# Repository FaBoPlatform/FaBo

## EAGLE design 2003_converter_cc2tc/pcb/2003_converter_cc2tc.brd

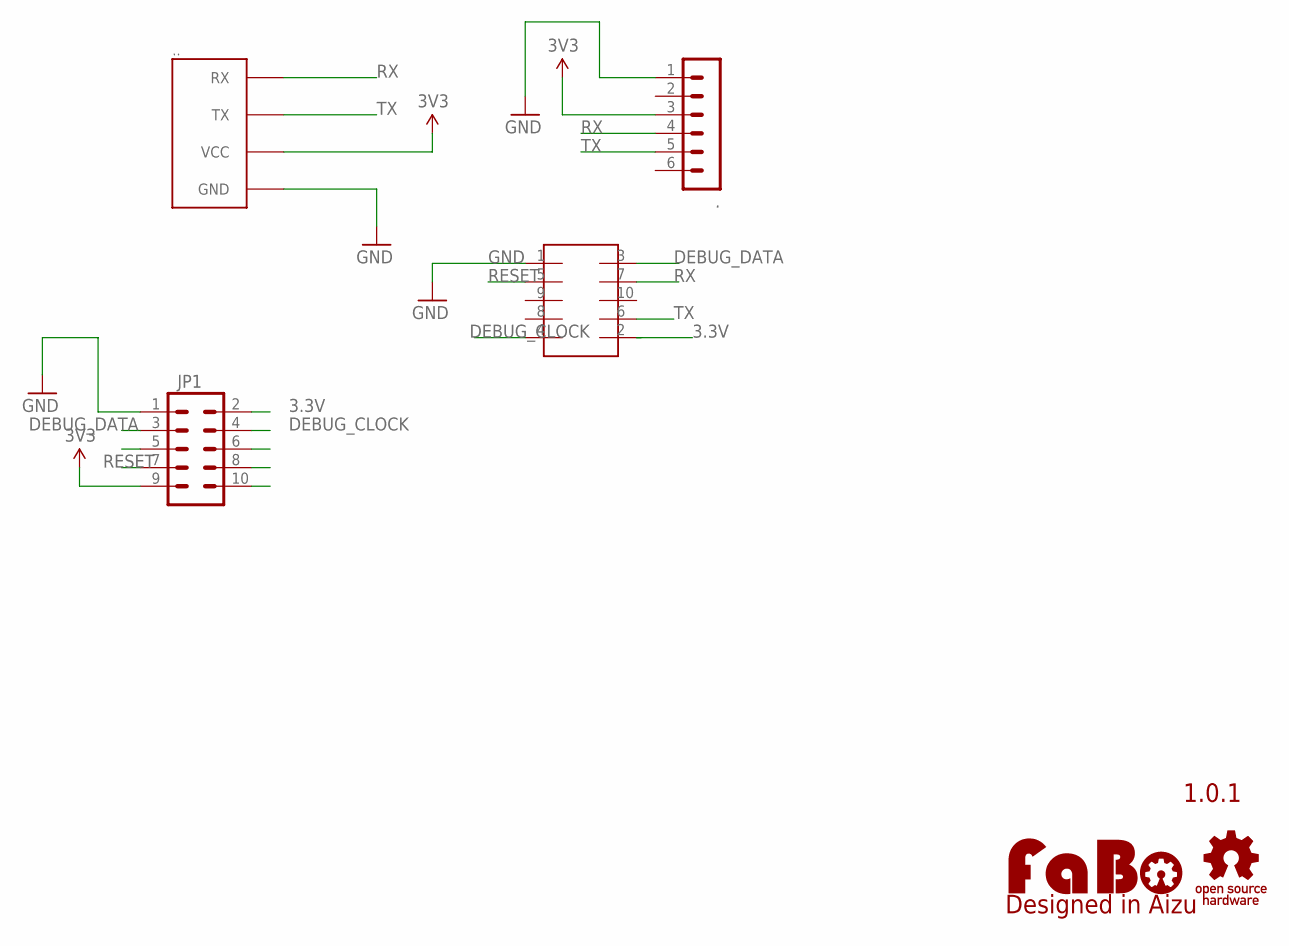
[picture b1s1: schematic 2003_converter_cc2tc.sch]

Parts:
.: MA06-1
..: FABO_BRICK_SERIAL-S04B-PASK-2; FABO_BRICK_SERIAL_S04B-PASK-2
JP1: M05X2SHD; 2X5-SHROUDED
U$1: LOGO_OSHW-M_BOTTOM; LOGO_OSHW_M_BOTTOM
U$2: LOGO_FABO-M; LOGO_FABO_MS
U$4: TC-2050-SOCKET

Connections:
3.3V: JP1.2, U$4.2
3V3: ..3, ...VCC, JP1.9
CSN: JP1.5
DEBUG_CLOCK: JP1.4, U$4.4
DEBUG_DATA: JP1.3, U$4.3
GND: ..1, ...GND, JP1.1, U$4.1
MISO: JP1.10
MOSI: JP1.8
RESET: JP1.7, U$4.5
RX: ..4, ...RX, U$4.7
SCLK: JP1.6
TX: ..5, ...TX, U$4.6

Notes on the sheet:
1.0.1

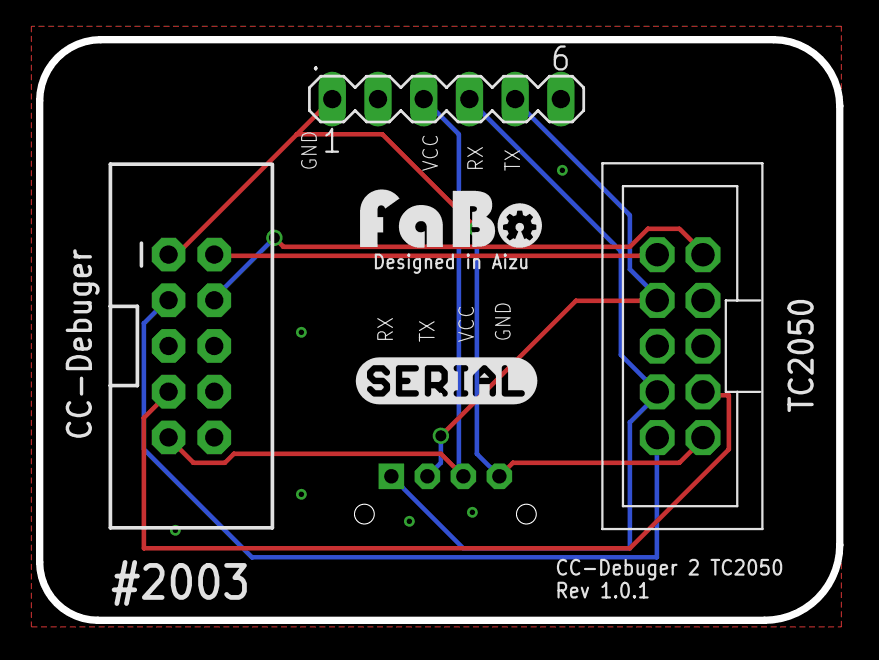
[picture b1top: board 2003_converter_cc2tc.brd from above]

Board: 2 copper layers, 44.4 x 32.3 mm, 7 parts (0 on the bottom side), 8 nets.

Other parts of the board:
U$5: LOGO_SILK_SERIAL2

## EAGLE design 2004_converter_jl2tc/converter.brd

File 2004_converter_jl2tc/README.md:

# #2004 Jlink 2 TagConnector

## Overview

JLinkからTagConnecterへの変換をおこないます。

## 回路図

## Github

https://github.com/FaBoPlatform/FaBo/tree/master/2004_converter_jl2tc

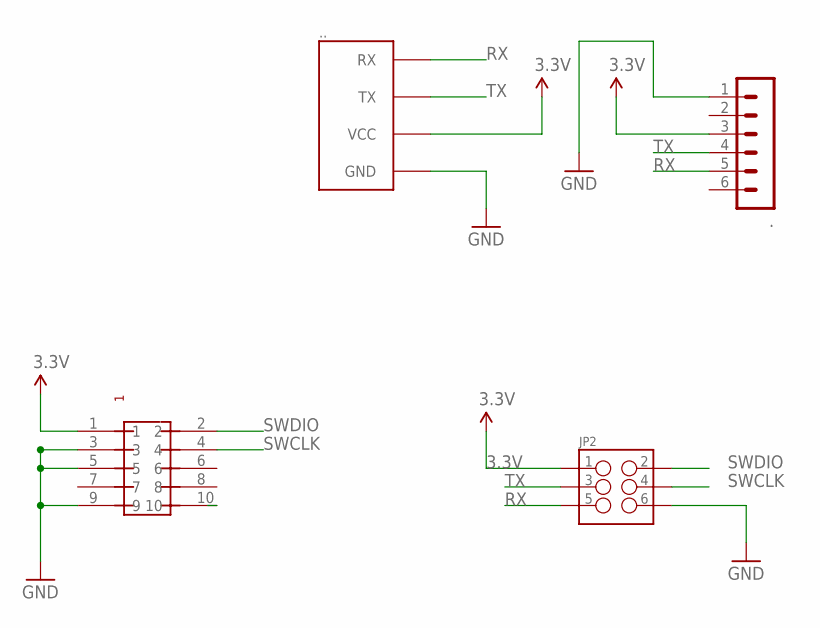
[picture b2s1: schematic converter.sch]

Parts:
.: MA06-1
..: FABO_BRICK_SERIAL-S04B-PASK-2; FABO_BRICK_SERIAL_S04B-PASK-2
JP2: M03X2; 2X3-SHROUDED
U$5: PIN-HEADER-SMT(1.27MM)2X5

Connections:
3.3V: ..3, ...VCC, JP2.1, U$5.1
GND: ..1, ...GND, JP2.6, U$5.3, U$5.5, U$5.9
RESET: U$5.10
RX: ..5, ...RX, JP2.5
SWCLK: JP2.4, U$5.4
SWDIO: JP2.2, U$5.2
TX: ..4, ...TX, JP2.3

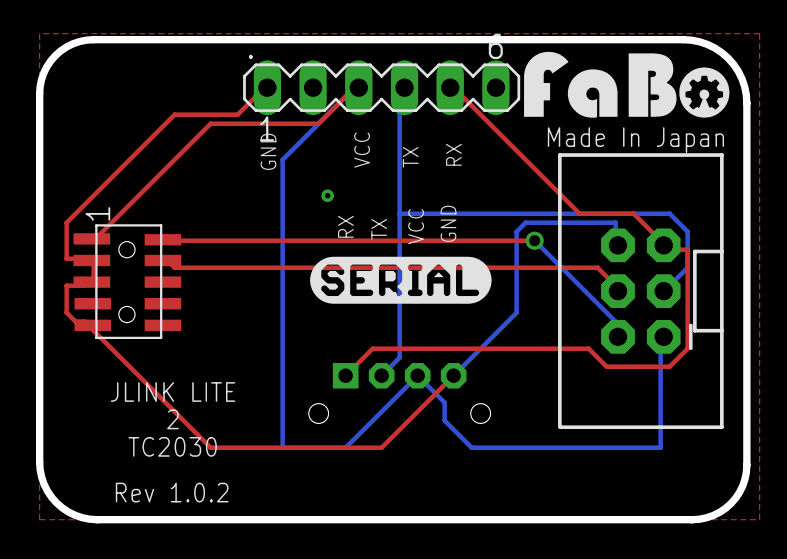
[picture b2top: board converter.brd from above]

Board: 2 copper layers, 39.3 x 26.7 mm, 6 parts (0 on the bottom side), 6 nets.

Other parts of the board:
U$1: LOGO_FABO_M
U$2: LOGO_SILK_SERIAL2

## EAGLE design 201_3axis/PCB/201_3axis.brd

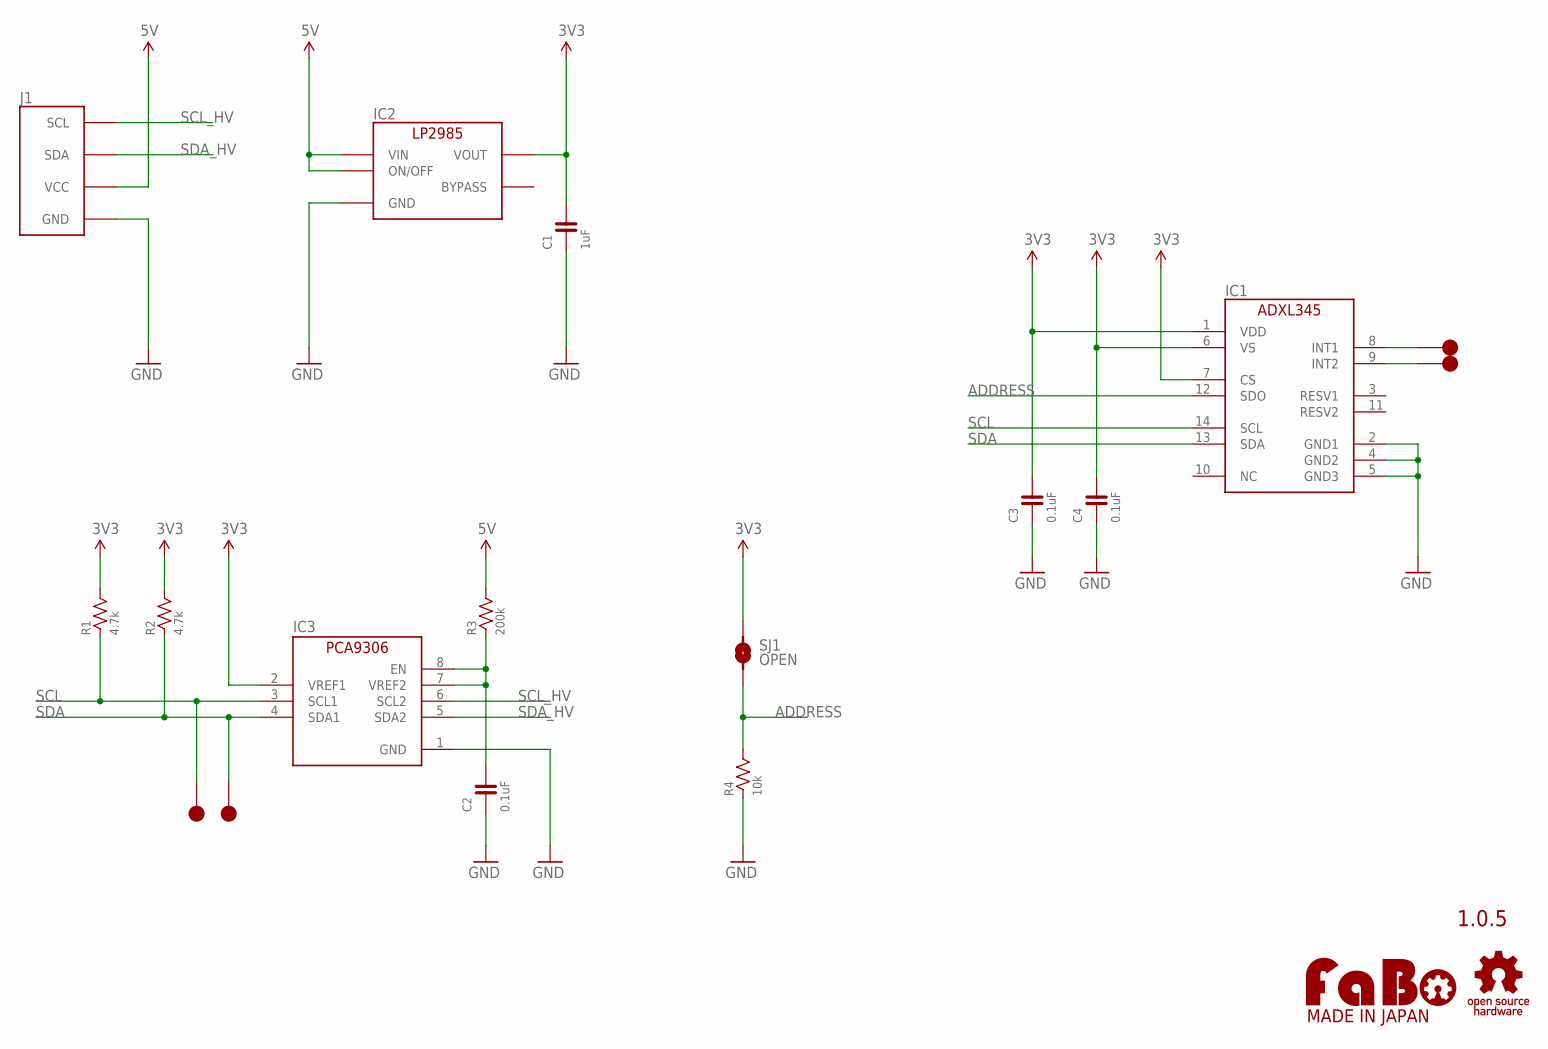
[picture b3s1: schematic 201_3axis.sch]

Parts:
C1: 1uF; 0603
C2, C3, C4: 0.1uF; 0603
IC1: AD-ADXL345; ANALOGDEVICES-ADXL345
IC2: LP2985-33DBV; SOT-23-5
IC3: PCA9306GM; XQFN8
J1: FABO_BRICK_I2C
R1, R2: 4.7k; 0603
R3: 200k; 0603
R4: 10k; 0603
SJ1: OPEN; SMD-JUMPER-2
TP1, TP2, TP3, TP4: TP-15
U$2: LOGO_OSHW-M_BOTTOM; LOGO_OSHW_M_BOTTOM
U$3: LOGO_FABO-M; LOGO_FABO_MS

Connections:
3V3: C1.2, C3.2, C4.2, IC1.1 (VDD), IC1.6 (VS), IC1.7 (CS), IC2.5 (VOUT), IC3.2 (VREF1), R1.2, R2.2, SJ1.1
5V: IC2.1 (VIN), IC2.3 (ON/OFF), J1.VCC, R3.2
ADDRESS: IC1.12 (SDO), R4.2, SJ1.2
GND: C1.1, C2.1, C3.1, C4.1, IC1.2 (GND1), IC1.4 (GND2), IC1.5 (GND3), IC2.2 (GND), IC3.1 (GND), J1.GND, R4.1
unnamed: C2.2, IC3.7 (VREF2), IC3.8 (EN), R3.1
unnamed: IC1.8 (INT1), TP3.1
unnamed: IC1.9 (INT2), TP4.1
SCL: IC1.14 (SCL), IC3.3 (SCL1), R1.1, TP2.1
SCL_HV: IC3.6 (SCL2), J1.SCL
SDA: IC1.13 (SDA), IC3.4 (SDA1), R2.1, TP1.1
SDA_HV: IC3.5 (SDA2), J1.SDA

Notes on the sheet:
1.0.5

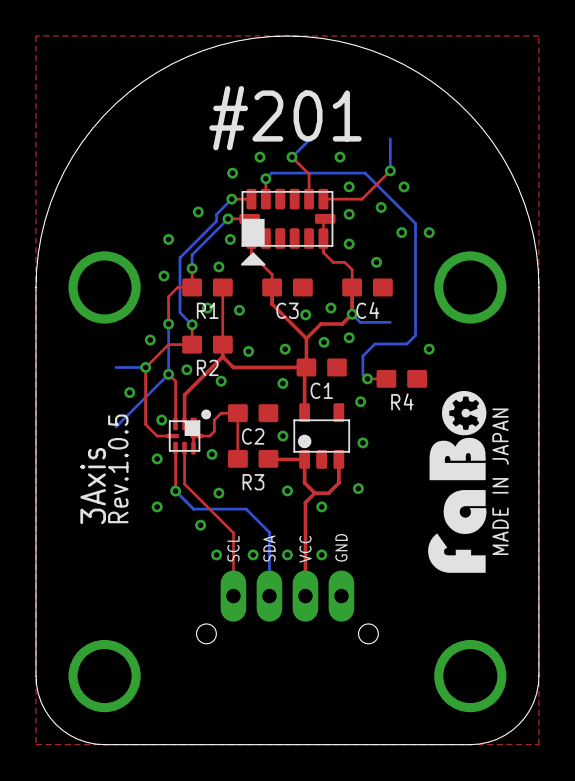
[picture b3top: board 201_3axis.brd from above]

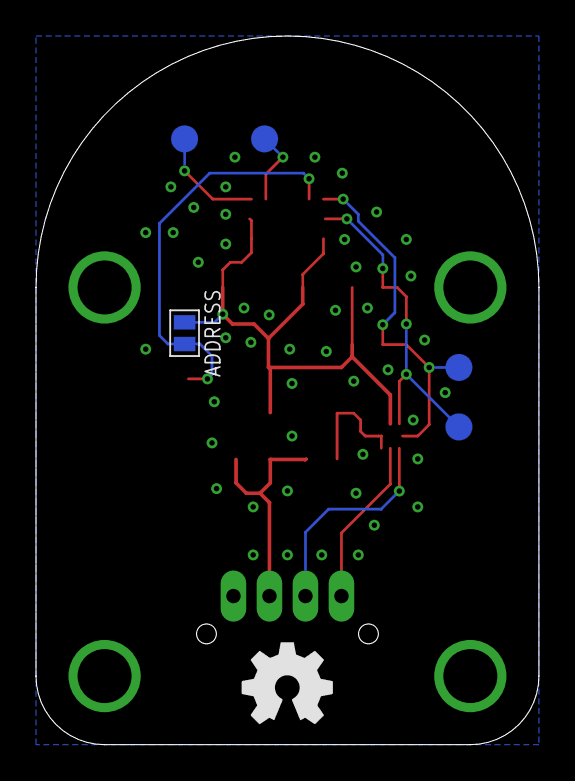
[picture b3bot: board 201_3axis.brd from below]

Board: 2 copper layers, 27.9 x 39.4 mm, 19 parts (5 on the bottom side), 11 nets.

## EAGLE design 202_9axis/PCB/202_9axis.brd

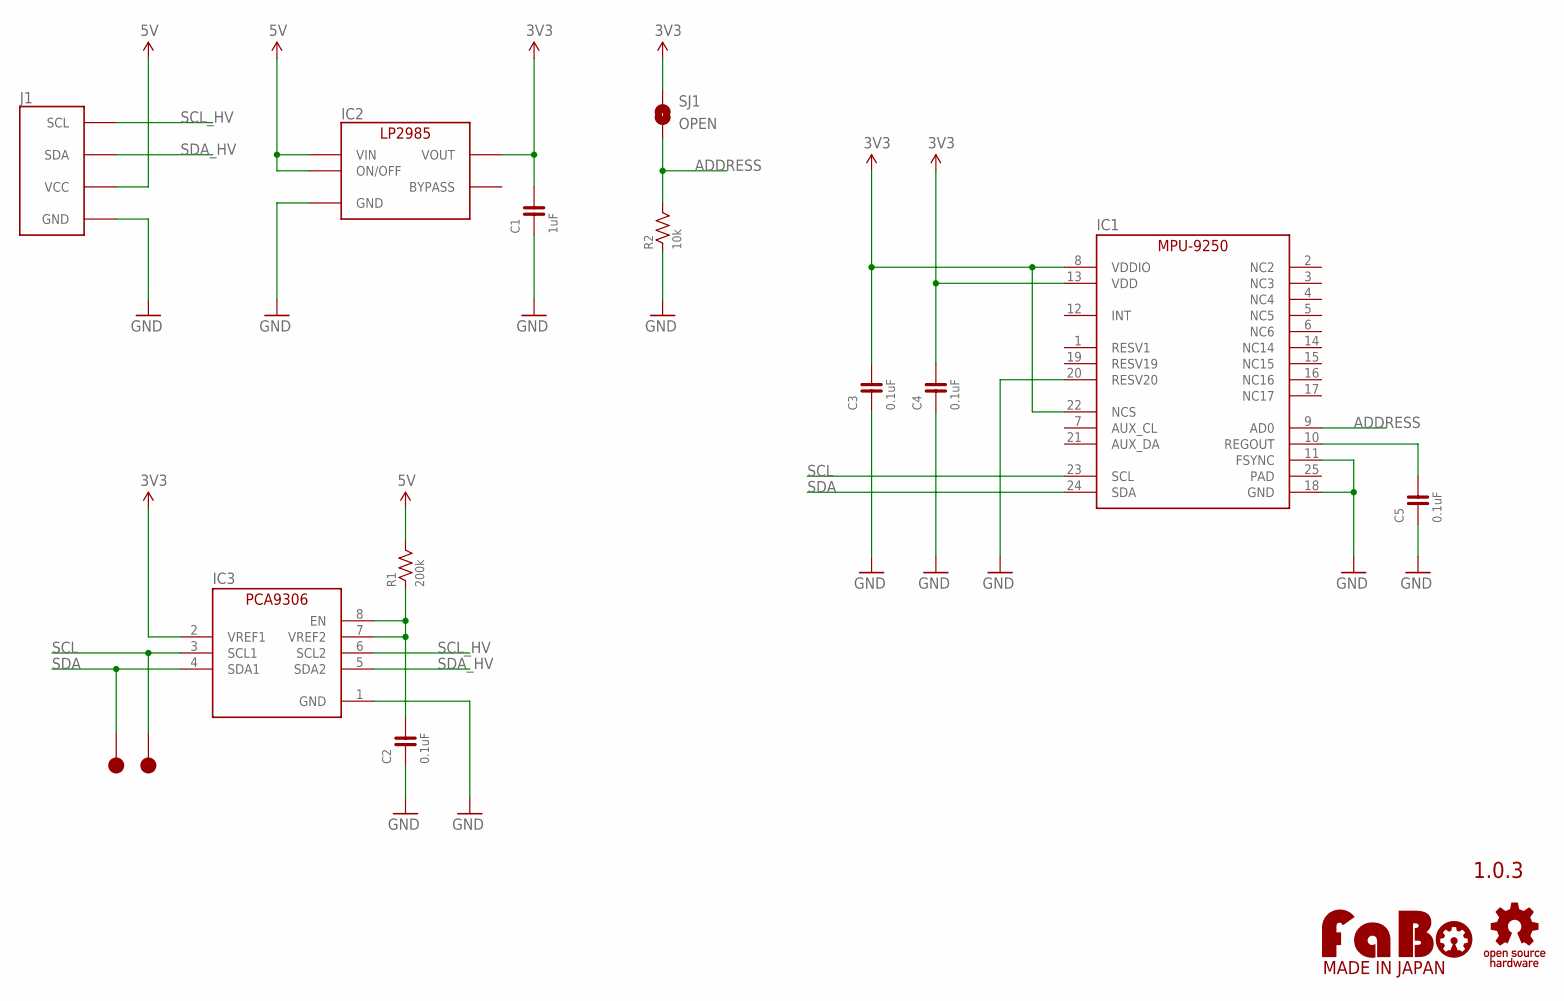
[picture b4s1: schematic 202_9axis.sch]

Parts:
C1: 1uF; 0603
C2, C3, C4, C5: 0.1uF; 0603
IC1: IS-MPU9250; INVENSENSE-MPU9250
IC2: TI-LP2985-33DBVR; TI-LP2985
IC3: PCA9306DQER; X2SON
J1: FABO_BRICK_I2C
R1: 200k; 0603
R2: 10k; 0603
SJ1: OPEN; SMD-JUMPER-2-OPEN
TP1, TP2: TP-10
U$2: LOGO_OSHW-M_BOTTOM; LOGO_OSHW_M_BOTTOM
U$3: LOGO_FABO-M; LOGO_FABO_MS

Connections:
3V3: C1.2, C3.2, C4.2, IC1.8 (VDDIO), IC1.13 (VDD), IC1.22 (NCS), IC2.5 (VOUT), IC3.2 (VREF1), SJ1.1
5V: IC2.1 (VIN), IC2.3 (ON/OFF), J1.VCC, R1.2
ADDRESS: IC1.9 (AD0), R2.2, SJ1.2
GND: C1.1, C2.1, C3.1, C4.1, C5.1, IC1.11 (FSYNC), IC1.18 (GND), IC1.20 (RESV20), IC2.2 (GND), IC3.1 (GND), J1.GND, R2.1
unnamed: C2.2, IC3.7 (VREF2), IC3.8 (EN), R1.1
REGOUT: C5.2, IC1.10 (REGOUT)
SCL: IC1.23 (SCL), IC3.3 (SCL1), TP2.1
SCL_HV: IC3.6 (SCL2), J1.SCL
SDA: IC1.24 (SDA), IC3.4 (SDA1), TP1.1
SDA_HV: IC3.5 (SDA2), J1.SDA

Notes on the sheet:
1.0.3

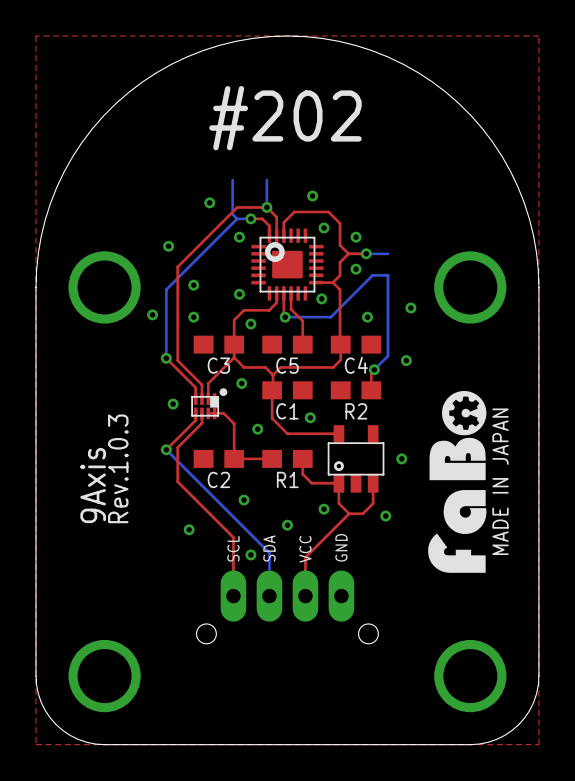
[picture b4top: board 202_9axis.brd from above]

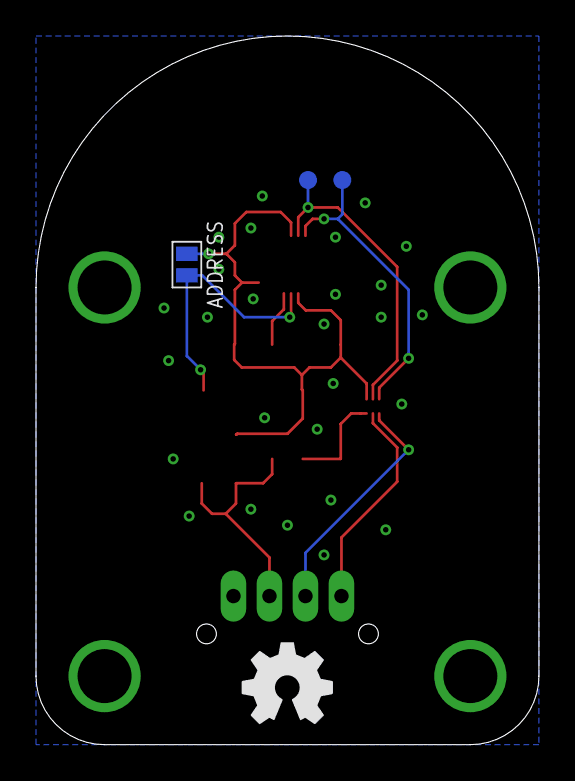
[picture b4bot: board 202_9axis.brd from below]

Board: 2 copper layers, 27.9 x 39.4 mm, 16 parts (3 on the bottom side), 10 nets.

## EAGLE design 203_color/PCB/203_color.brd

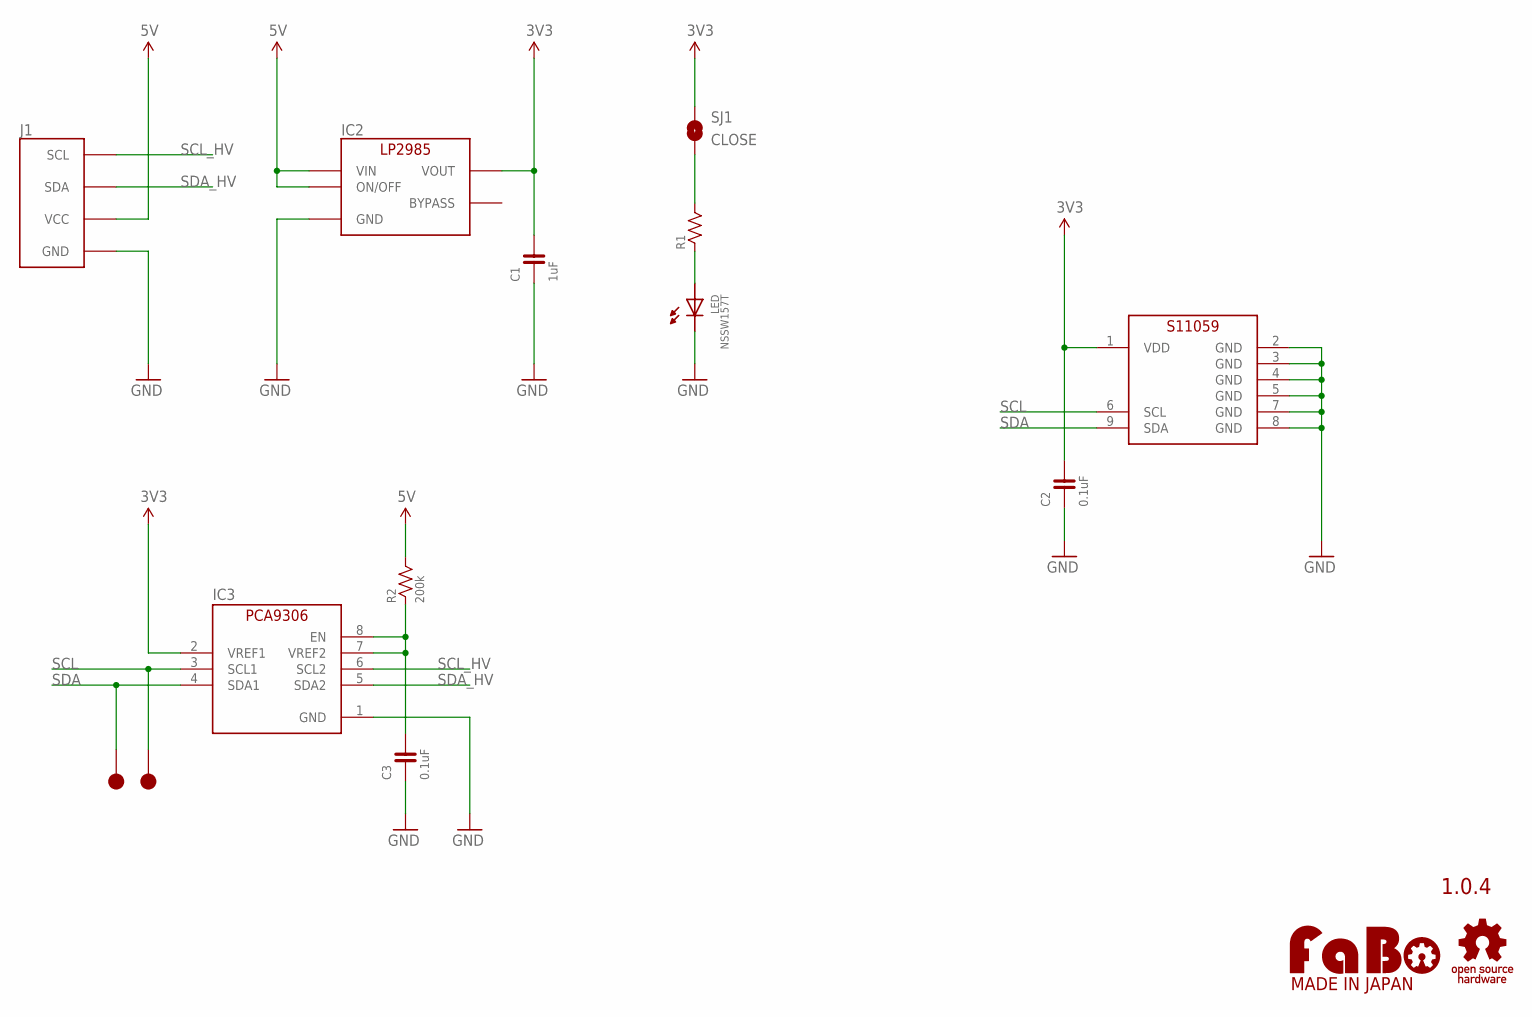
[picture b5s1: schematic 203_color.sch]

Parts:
C1: 1uF; 0603
C2, C3: 0.1uF; 0603
IC1: HAMAMATSU-S11059
IC2: TI-LP2985-33DBVR; TI-LP2985
IC3: PCA9306DQER; X2SON
J1: FABO_BRICK_I2C
LED: NSSW157T
R1: RESISTOR-0603; 0603
R2: 200k; 0603
SJ1: CLOSE; SMD-JUMPER-2-CLOSE
TP1, TP2: TP-10
U$2: LOGO_OSHW-M_BOTTOM; LOGO_OSHW_M_BOTTOM
U$3: LOGO_FABO-M; LOGO_FABO_MS

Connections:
3V3: C1.2, C2.2, IC1.1 (VDD), IC2.5 (VOUT), IC3.2 (VREF1), SJ1.1
5V: IC2.1 (VIN), IC2.3 (ON/OFF), J1.VCC, R2.2
GND: C1.1, C2.1, C3.1, IC1.2 (GND), IC1.3 (GND), IC1.4 (GND), IC1.5 (GND), IC1.7 (GND), IC1.8 (GND), IC2.2 (GND), IC3.1 (GND), J1.GND, LED.CATHODE1 (CATHODE), LED.CATHODE2 (CATHODE)
unnamed: LED.ANODE1 (ANODE), LED.ANODE2 (ANODE), R1.1
unnamed: C3.2, IC3.7 (VREF2), IC3.8 (EN), R2.1
unnamed: R1.2, SJ1.2
SCL: IC1.6 (SCL), IC3.3 (SCL1), TP2.1
SCL_HV: IC3.6 (SCL2), J1.SCL
SDA: IC1.9 (SDA), IC3.4 (SDA1), TP1.1
SDA_HV: IC3.5 (SDA2), J1.SDA

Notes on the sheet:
1.0.4

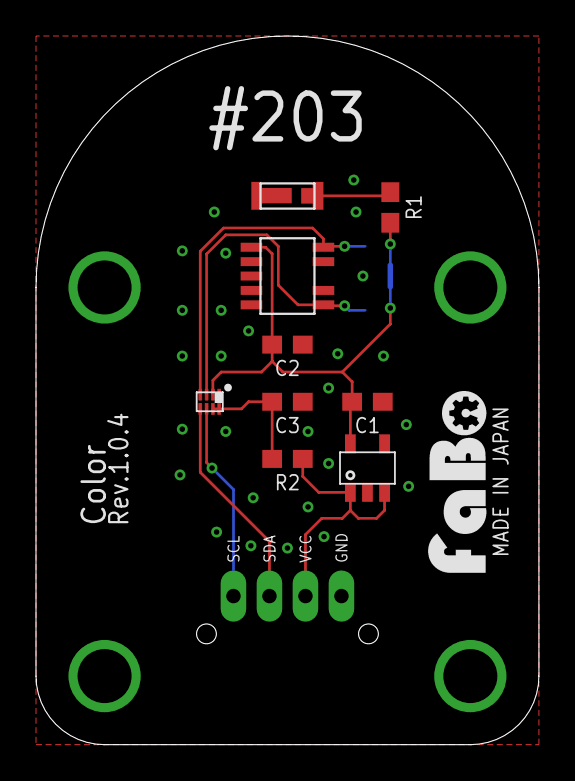
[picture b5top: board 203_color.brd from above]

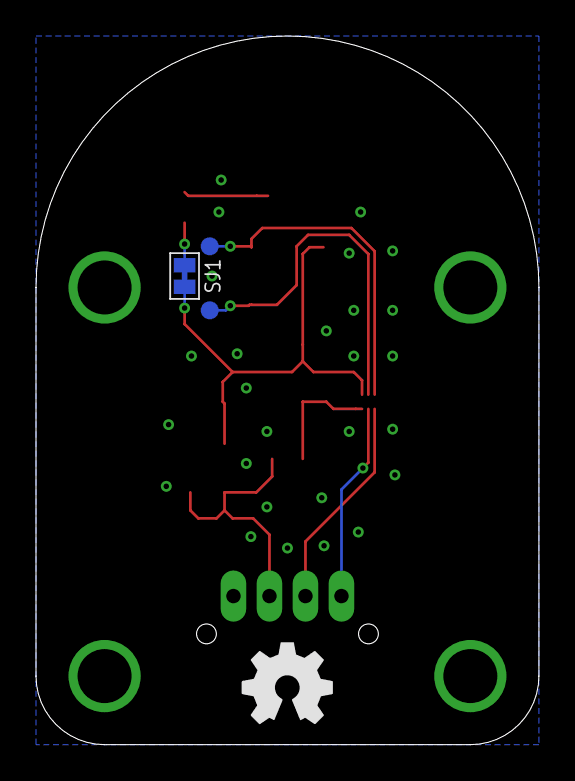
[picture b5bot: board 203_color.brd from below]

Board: 2 copper layers, 27.9 x 39.4 mm, 15 parts (3 on the bottom side), 10 nets.

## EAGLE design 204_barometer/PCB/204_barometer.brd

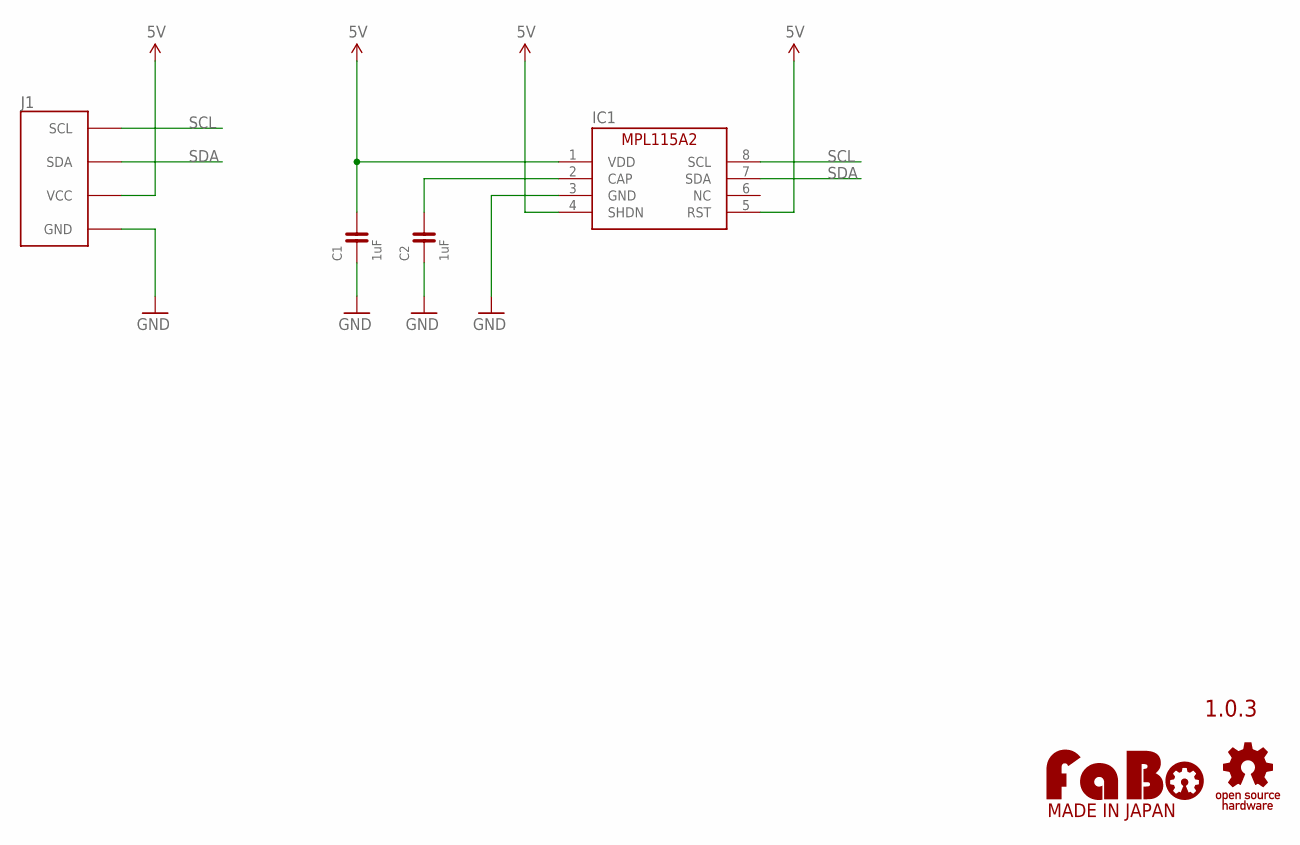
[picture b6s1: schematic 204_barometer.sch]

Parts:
C1, C2: 1uF; 0603
IC1: FS-MPL115A2; FREESCALE-MPL115A2
J1: FABO_BRICK_I2C
U$2: LOGO_OSHW-M_BOTTOM; LOGO_OSHW_M_BOTTOM
U$4: LOGO_FABO-M; LOGO_FABO_MS

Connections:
5V: C1.2, IC1.1 (VDD), IC1.4 (SHDN), IC1.5 (RST), J1.VCC
GND: C1.1, C2.1, IC1.3 (GND), J1.GND
unnamed: C2.2, IC1.2 (CAP)
SCL: IC1.8 (SCL), J1.SCL
SDA: IC1.7 (SDA), J1.SDA

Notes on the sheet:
1.0.3

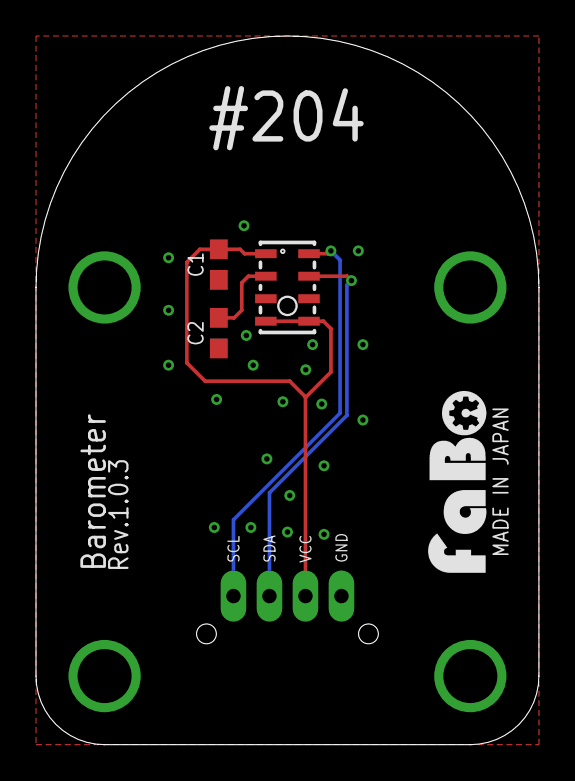
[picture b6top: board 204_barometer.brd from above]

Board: 2 copper layers, 27.9 x 39.4 mm, 6 parts (0 on the bottom side), 5 nets.

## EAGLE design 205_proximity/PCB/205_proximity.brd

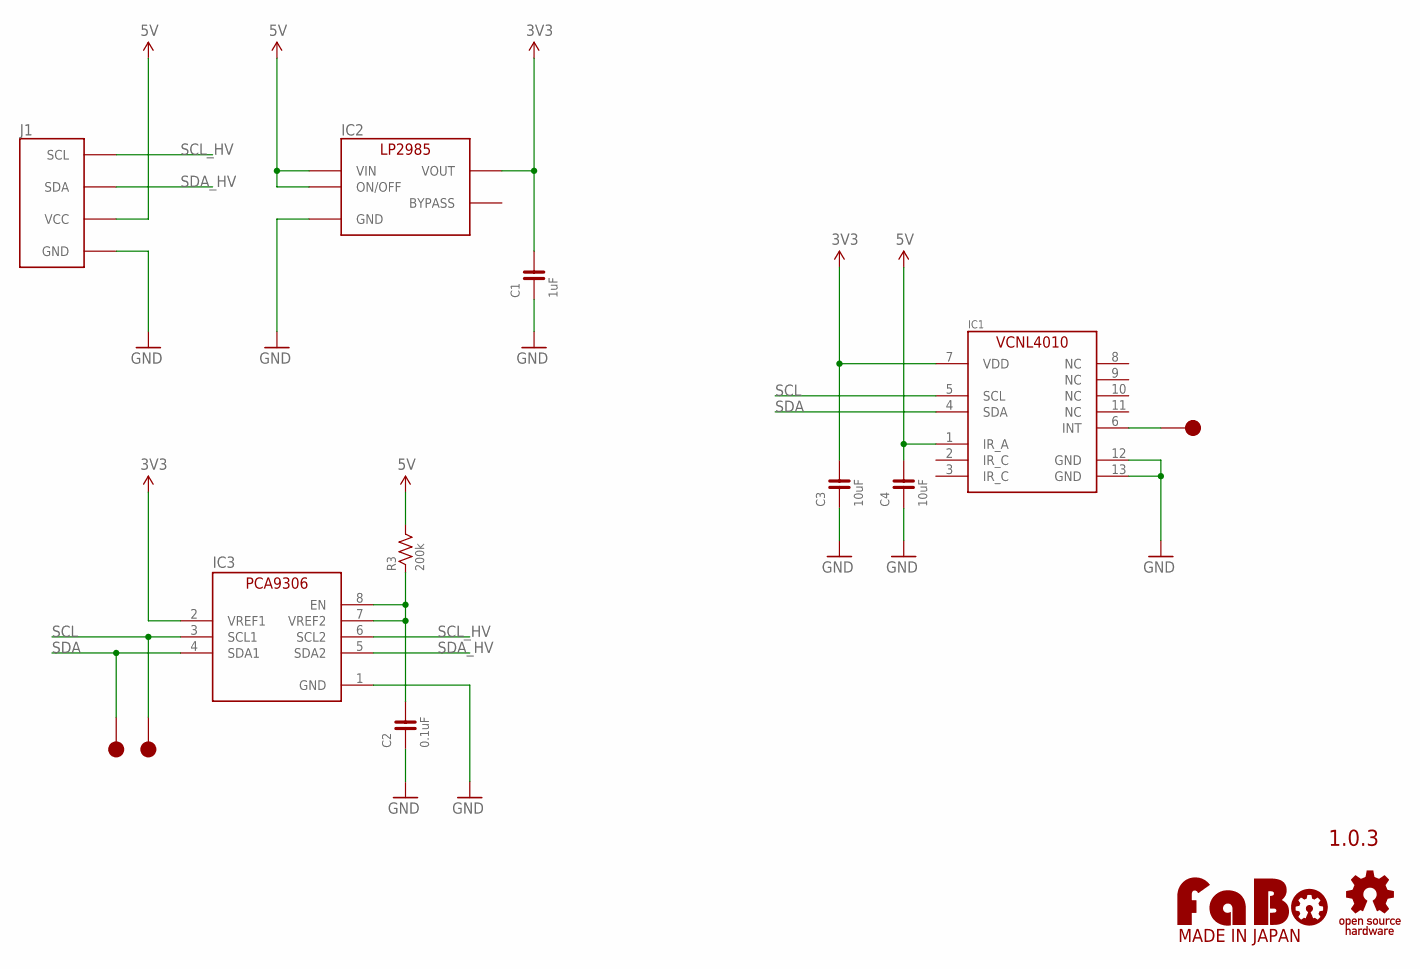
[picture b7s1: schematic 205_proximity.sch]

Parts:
C1: 1uF; 0603
C2: 0.1uF; 0603
C3, C4: 10uF; 0603
IC1: VCNL4010; VCNL4010-GS08
IC2: TI-LP2985-33DBVR; TI-LP2985
IC3: PCA9306DQER; X2SON
J1: FABO_BRICK_I2C
R3: 200k; 0603
TP1, TP2, TP3: TP-10
U$2: LOGO_OSHW-M_BOTTOM; LOGO_OSHW_M_BOTTOM
U$3: LOGO_FABO-M; LOGO_FABO_MS

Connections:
3V3: C1.2, C3.2, IC1.7 (VDD), IC2.5 (VOUT), IC3.2 (VREF1)
5V: C4.2, IC1.1 (IR_A), IC2.1 (VIN), IC2.3 (ON/OFF), J1.VCC, R3.2
GND: C1.1, C2.1, C3.1, C4.1, IC1.12 (GND), IC1.13 (GND), IC2.2 (GND), IC3.1 (GND), J1.GND
unnamed: C2.2, IC3.7 (VREF2), IC3.8 (EN), R3.1
unnamed: IC1.6 (INT), TP3.1
SCL: IC1.5 (SCL), IC3.3 (SCL1), TP2.1
SCL_HV: IC3.6 (SCL2), J1.SCL
SDA: IC1.4 (SDA), IC3.4 (SDA1), TP1.1
SDA_HV: IC3.5 (SDA2), J1.SDA

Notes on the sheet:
1.0.3

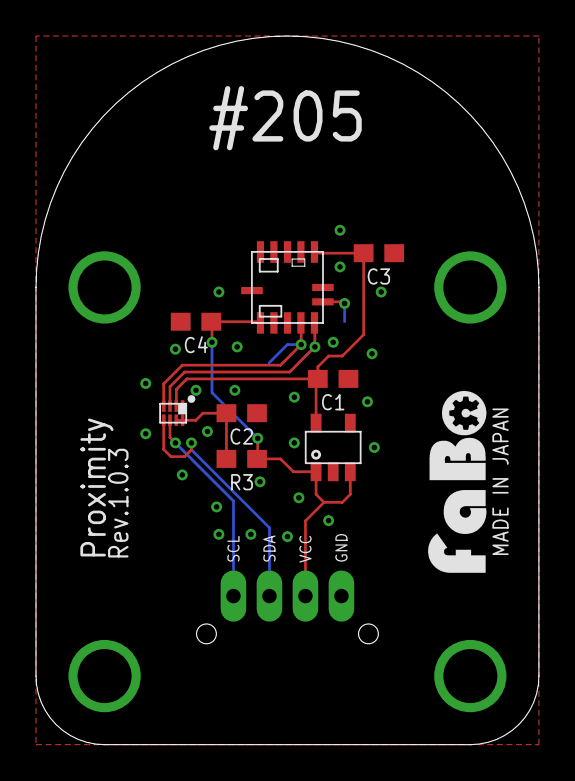
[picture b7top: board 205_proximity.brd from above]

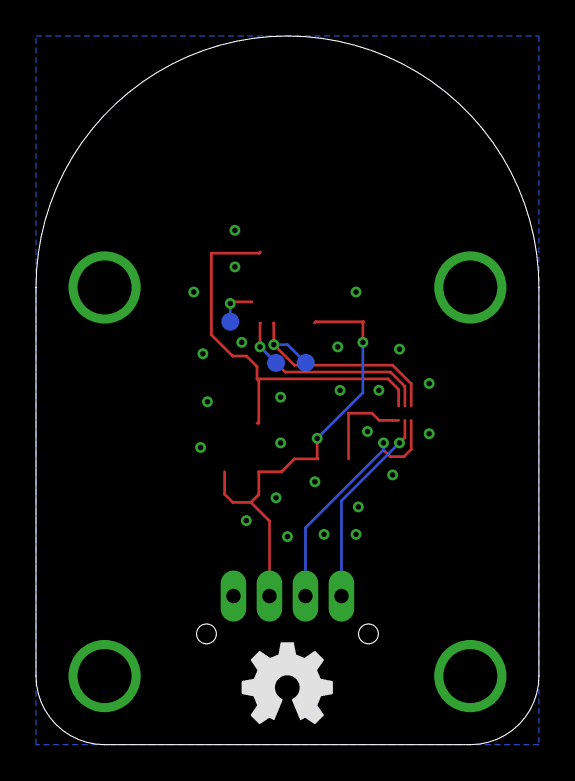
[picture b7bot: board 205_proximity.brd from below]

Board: 2 copper layers, 27.9 x 39.4 mm, 14 parts (3 on the bottom side), 9 nets.

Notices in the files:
parts and their libraries:
SparkFun-Connectors: Licensing: CC v3.0 Share-Alike You are welcome to use this library for commercial purposes.
FaBo-etc: Released under the Creative Commons Attribution-ShareAlike 4.0 License
https://creativecommons.org/licenses/by-sa/4.0
GClue: Released under the Creative Commons
